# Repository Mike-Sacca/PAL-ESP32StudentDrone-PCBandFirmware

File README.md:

# Modified ESP-FLY Drone Firmware

## Project Overview

This repository contains a modified firmware branch for an ESP32-S3-based educational micro-quadcopter.

The firmware in this repository was not developed entirely from scratch. It is derived from the open-source firmware distributed as part of the **ESP-FLY DIY Drone Kit**, a collaborative project created by **Seeed Studio** and **Max Imagination**.

This modified branch is intended for educational use, experimentation, hardware adaptation, and continued open-source development.

## Primary Upstream Project

**Project:** ESP-FLY DIY Drone Kit
**Creators:** Seeed Studio and Max Imagination
**Official repository:**
https://github.com/Seeed-Projects/Co-Create_ESP-FLY

The original ESP-FLY repository provides firmware, hardware information, and supporting resources for a micro-quadcopter built around the Seeed Studio XIAO ESP32S3.

Full credit for the original ESP-FLY project, its firmware adaptation, and its supporting educational resources belongs to Seeed Studio, Max Imagination, and the respective upstream contributors.

## Additional Upstream Acknowledgments

The ESP-FLY firmware identifies itself as a modified version of or successor to software from the following projects.

### Espressif ESP-Drone

**Developer:** Espressif Systems
**Repository:**
https://github.com/espressif/esp-drone

ESP-Drone is an open-source ESP32 drone firmware platform supporting Wi-Fi control, Crazyflie-compatible communication, sensor processing, and flight stabilization.

### Circuit Digest ESP-Drone Modification

The ESP-FLY firmware also credits firmware modifications produced by **Circuit Digest**.

Applicable attribution, copyright, and license notices contained in the original ESP-FLY source files have been retained in this branch.

### Bitcraze Crazyflie

Portions of the underlying flight-control architecture originate from or are based on the open-source Crazyflie project by Bitcraze.

**Project website:**
https://www.bitcraze.io/

**Repository:**
https://github.com/bitcraze/crazyflie-firmware

The Crazyflie project provided important foundations for flight control, communication, and stabilization systems subsequently adapted for ESP-Drone and ESP-FLY.

## Modifications in This Branch

This repository contains modifications made or maintained by:

**Maintainer:** Michael Sacca
**Modification period:** May 20, 2026–present

Changes in this branch may include:

* Hardware pin and GPIO remapping
* Support for a custom flight-controller PCB
* Motor-output configuration changes
* Sensor or IMU configuration changes
* Flight-control parameter adjustments
* Compatibility changes for the Seeed Studio XIAO ESP32S3
* Educational documentation and deployment changes
* Other modifications documented in the Git commit history

This branch is an independent modification and should not be interpreted as an official firmware release from Seeed Studio, Max Imagination, Espressif Systems, Circuit Digest, or Bitcraze.

Problems introduced by this modified branch should be reported to this branch’s maintainer rather than to the original project creators unless the issue is confirmed to exist in the upstream software.

## License

This software is distributed under the **GNU General Public License, Version 3.0**, consistent with the license of the upstream ESP-FLY repository.

You may use, study, modify, and redistribute this software under the terms of the GNU General Public License v3.0.

When redistributing this firmware or a modified version of it, you must comply with the GPL v3.0 requirements, including the following where applicable:

1. Retain applicable copyright, attribution, license, and warranty notices.
2. Clearly state that the software has been modified.
3. Include a relevant modification date or modification history.
4. Distribute covered modifications under the GNU General Public License v3.0.
5. Make the corresponding source code available in the manner required by the license.
6. Include a copy of the GNU General Public License v3.0 with the distributed software.

The complete license text should be included in this repository as a file named `LICENSE`.

A copy of the GNU General Public License v3.0 is also available at:

https://www.gnu.org/licenses/gpl-3.0.html

## Warranty and Safety Disclaimer

This software is provided **“AS IS,” WITHOUT WARRANTY OF ANY KIND**, express or implied, including but not limited to warranties of merchantability, fitness for a particular purpose, and noninfringement.

Drone firmware controls physical hardware and rotating propellers. Improper assembly, configuration, modification, or operation may result in property damage or personal injury.

Users are responsible for:

* Reviewing the source code and configuration
* Safely testing all modifications
* Removing propellers during initial bench testing
* Operating the aircraft in an appropriate test area
* Complying with applicable laws, regulations, and safety requirements

The upstream creators and contributors are not responsible for problems, damage, or injuries caused by modifications made in this branch.

## Educational Use

This modified branch is maintained primarily for educational and experimental use.

Use of the firmware in a class, workshop, camp, or nonprofit educational activity does not transfer ownership of the upstream software.

Students and participants should be informed that the firmware is built upon open-source work created by Seeed Studio, Max Imagination, Espressif Systems, Circuit Digest, Bitcraze, and other contributors.

Users are encouraged to visit the original projects, review their documentation, and support their creators.

## Suggested Attribution

When referencing this firmware in educational materials, presentations, or project documentation, the following attribution may be used:

> This firmware is a modified branch of the open-source ESP-FLY firmware created through the Seeed Studio and Max Imagination Co-Create project. ESP-FLY is derived from Espressif’s ESP-Drone firmware and other credited open-source contributions. The software is distributed under the GNU General Public License v3.0.

## Original Project Links

* **ESP-FLY by Seeed Studio and Max Imagination:**
  https://github.com/Seeed-Projects/Co-Create_ESP-FLY

* **Espressif ESP-Drone:**
  https://github.com/espressif/esp-drone

* **Bitcraze Crazyflie firmware:**
  https://github.com/bitcraze/crazyflie-firmware

* **GNU General Public License v3.0:**
  https://www.gnu.org/licenses/gpl-3.0.html

## Acknowledgments

Special thanks to:

* Seeed Studio
* Max Imagination
* Espressif Systems
* Circuit Digest
* Bitcraze
* All individual contributors to ESP-FLY, ESP-Drone, Crazyflie, and their incorporated open-source components

Their work made this modified educational firmware branch possible.

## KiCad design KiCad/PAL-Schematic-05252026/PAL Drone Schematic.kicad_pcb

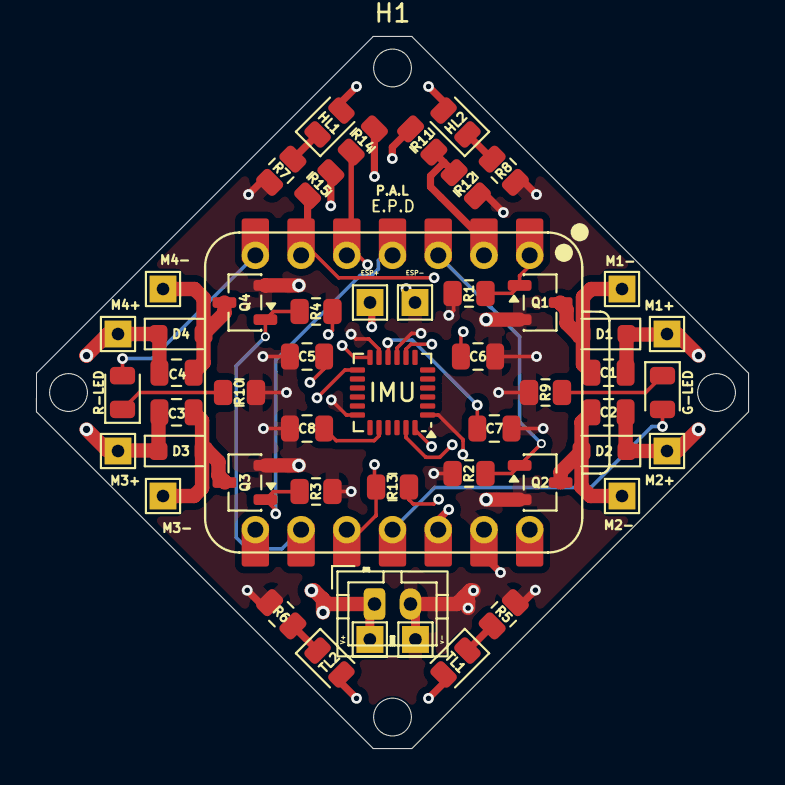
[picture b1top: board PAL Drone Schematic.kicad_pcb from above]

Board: 6 copper layers, 39.6 x 39.6 mm, 56 parts (0 on the bottom side), 25 nets.

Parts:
C1, C2, C3, C4, C5, C7: 0.1uF; C_0805_2012Metric
C6, C8: 0.01uF; C_0805_2012Metric
D1, D2, D3, D4: 1N4148WS; D_SOD-323_HandSoldering
E.P.D: XIAO-ESP32-S3-DIP
ESP+: TestPoint; TestPoint_THTPad_1.5x1.5mm_Drill0.7mm
ESP-: TestPoint; TestPoint_THTPad_1.5x1.5mm_Drill0.7mm
G-LED: LED; LED_0805_2012Metric
H1, H2, H3, H4: MountingHole; MountingHole_2.1mm
HL1, HL2: LED; LED_0805_2012Metric
IMU: MPU-6050; InvenSense_QFN-24_4x4mm_P0.5mm
M1+, M1-, M2+, M2-, M3+, M3-, M4+, M4-: TP; TestPoint_THTPad_1.5x1.5mm_Drill0.7mm
P.A.L: Conn_01x02; JST_PH_B2B-PH-K_1x02_P2.00mm_Vertical
Q1, Q2, Q3, Q4: SI2300DS-T1-GE3; SOT-23-3
R1, R2, R3, R4, R13, R14, R15: 10k; R_0805_2012Metric
R5, R6: 150; R_0805_2012Metric
R7, R8: 100; R_0805_2012Metric
R9, R10: 200; R_0805_2012Metric
R11, R12: 10K; R_0805_2012Metric
R-LED: LED; LED_0805_2012Metric
TL1, TL2: LED; LED_0805_2012Metric
V+: TP; TestPoint_THTPad_1.5x1.5mm_Drill0.7mm
v-: TP; TestPoint_THTPad_1.5x1.5mm_Drill0.7mm

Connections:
+3.3V: C5.1, C6.1, E.P.D.12 (3V3), HL1.2 (A), HL2.2 (A), IMU.8 (VLOGIC), IMU.13 (VDD), R13.1, R14.2, R15.1, TL1.2 (A), TL2.2 (A)
GND: C5.2, C6.2, C7.2, C8.2, E.P.D.13 (GND), ESP-.1 (1_1), IMU.1 (CLKIN), IMU.9 (AD0), IMU.11 (FSYNC), IMU.18 (GND), P.A.L.2, Q1.2 (S), Q2.2 (S), Q3.2 (S), Q4.2 (S), R1.1, R2.1, R3.1, R4.1, R5.2, R6.2, R7.2, R8.2, R9.1, R10.1, R12.2, v-.1 (1_1)
unnamed: C1.2, D1.2 (A), M1-.1 (1_1), Q1.3 (D)
unnamed: C2.2, D2.2 (A), M2-.1 (1_1), Q2.3 (D)
unnamed: C3.2, D3.2 (A), M3-.1 (1_1), Q3.3 (D)
unnamed: C4.2, D4.2 (A), M4-.1 (1_1), Q4.3 (D)
unnamed: E.P.D.11 (GPIO9_A10_D10_MOSI), G-LED.2 (A)
unnamed: G-LED.1 (K), R9.2
unnamed: HL1.1 (K), R7.1
unnamed: HL2.1 (K), R8.1
unnamed: E.P.D.1 (GPIO1_A0_D0), Q1.1 (G), R1.2
unnamed: E.P.D.3 (GPIO3_A2_D2), Q2.1 (G), R2.2
unnamed: E.P.D.4 (GPIO4_A3_D3), Q3.1 (G), R3.2
unnamed: E.P.D.9 (GPIO7_A8_D8_SCK), Q4.1 (G), R4.2
unnamed: E.P.D.7 (GPIO43_D6_TX), R-LED.2 (A)
unnamed: R10.2, R-LED.1 (K)
unnamed: R5.1, TL1.1 (K)
unnamed: R6.1, TL2.1 (K)
unnamed: C8.1, IMU.20 (CPOUT)
unnamed: E.P.D.10 (GPIO8_A9_D9_MISO), IMU.12 (INT), R13.2
unnamed: C7.1, IMU.10 (REGOUT)
unnamed: E.P.D.6 (GPIO6_A5_D5_SCL), IMU.23 (SCL), R15.2
unnamed: E.P.D.5 (GPIO5_A4_D4_SDA), IMU.24 (SDA), R14.1
unnamed: E.P.D.2 (GPIO2_A1_D1), R11.2, R12.1
VBat_3.7V: C1.1, C2.1, C3.1, C4.1, D1.1 (K), D2.1 (K), D3.1 (K), D4.1 (K), ESP+.1 (1_1), M1+.1 (1_1), M2+.1 (1_1), M3+.1 (1_1), M4+.1 (1_1), P.A.L.1, R11.1, V+.1 (1_1)
